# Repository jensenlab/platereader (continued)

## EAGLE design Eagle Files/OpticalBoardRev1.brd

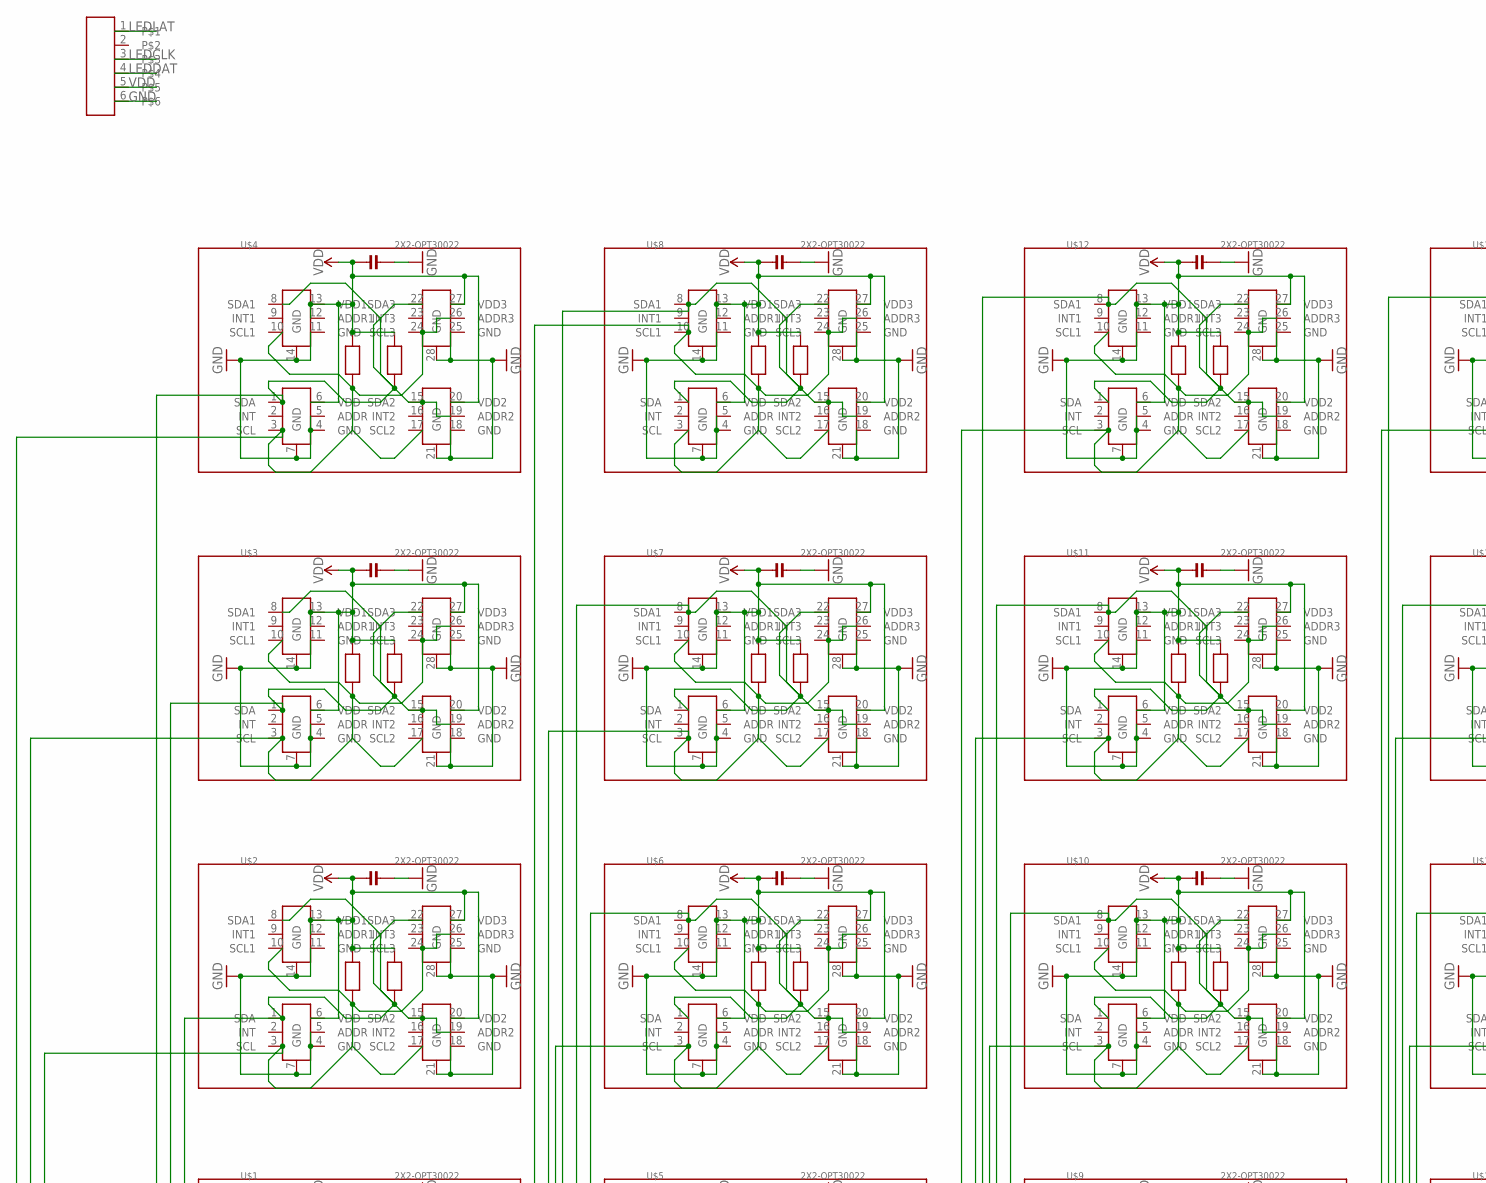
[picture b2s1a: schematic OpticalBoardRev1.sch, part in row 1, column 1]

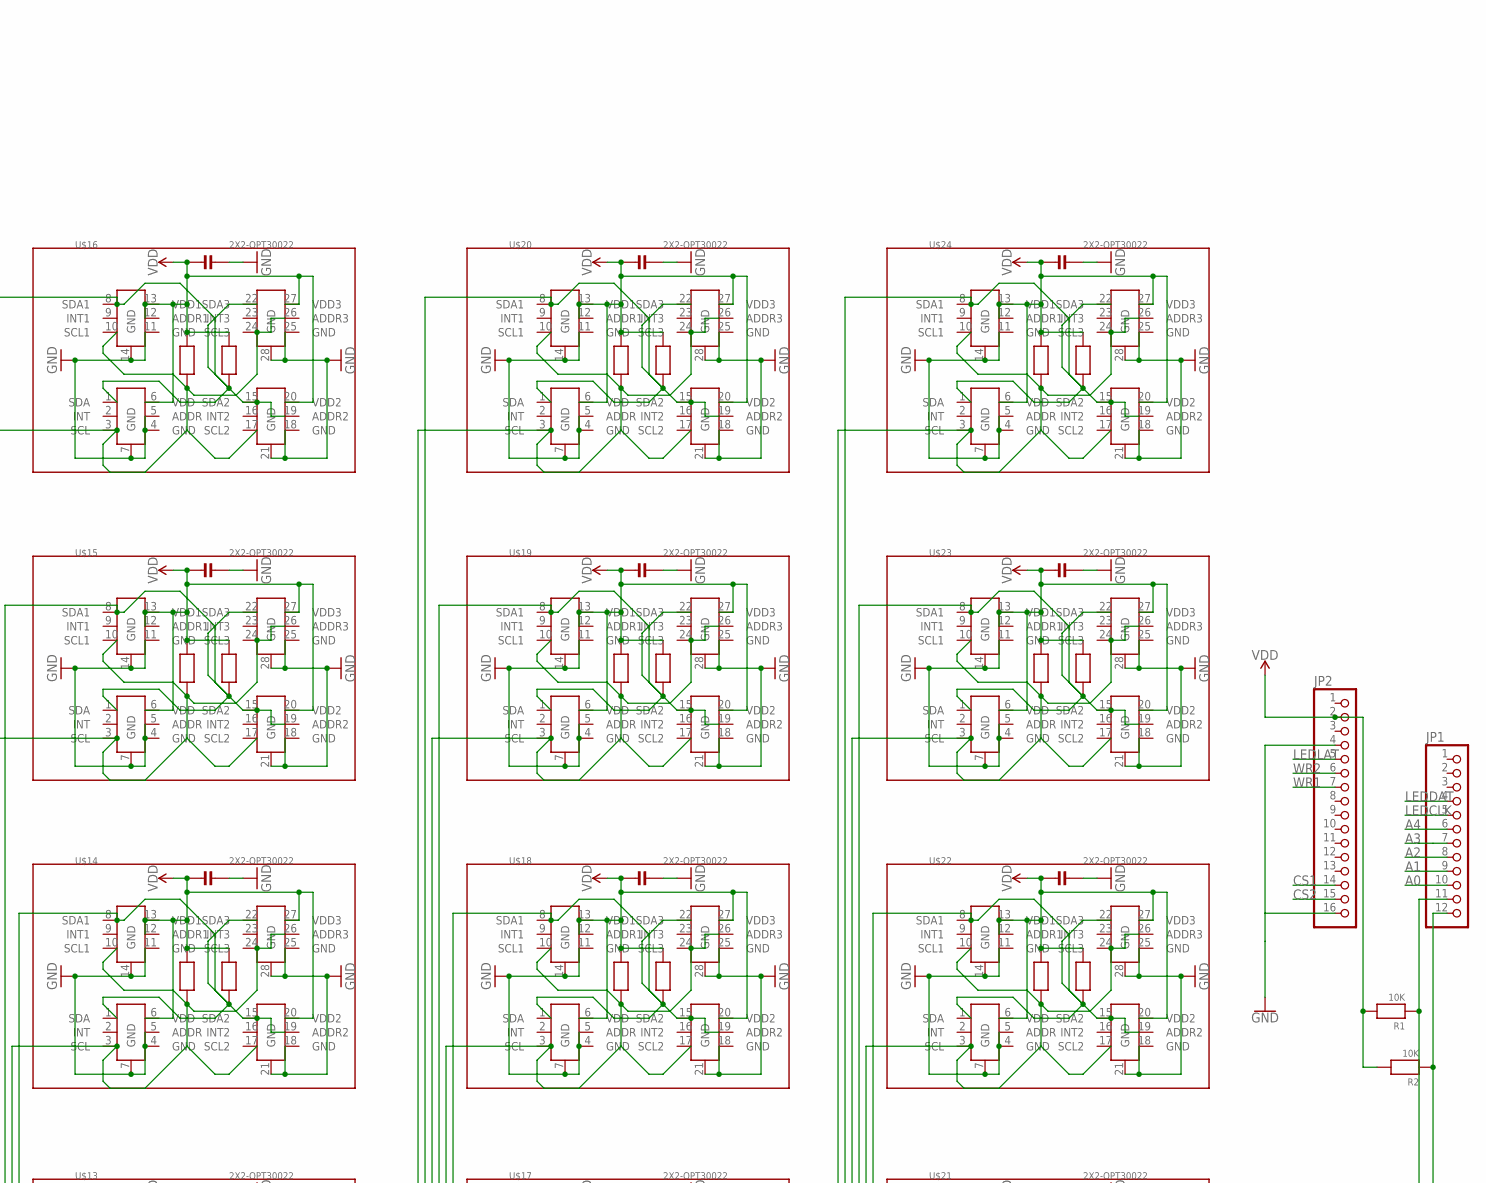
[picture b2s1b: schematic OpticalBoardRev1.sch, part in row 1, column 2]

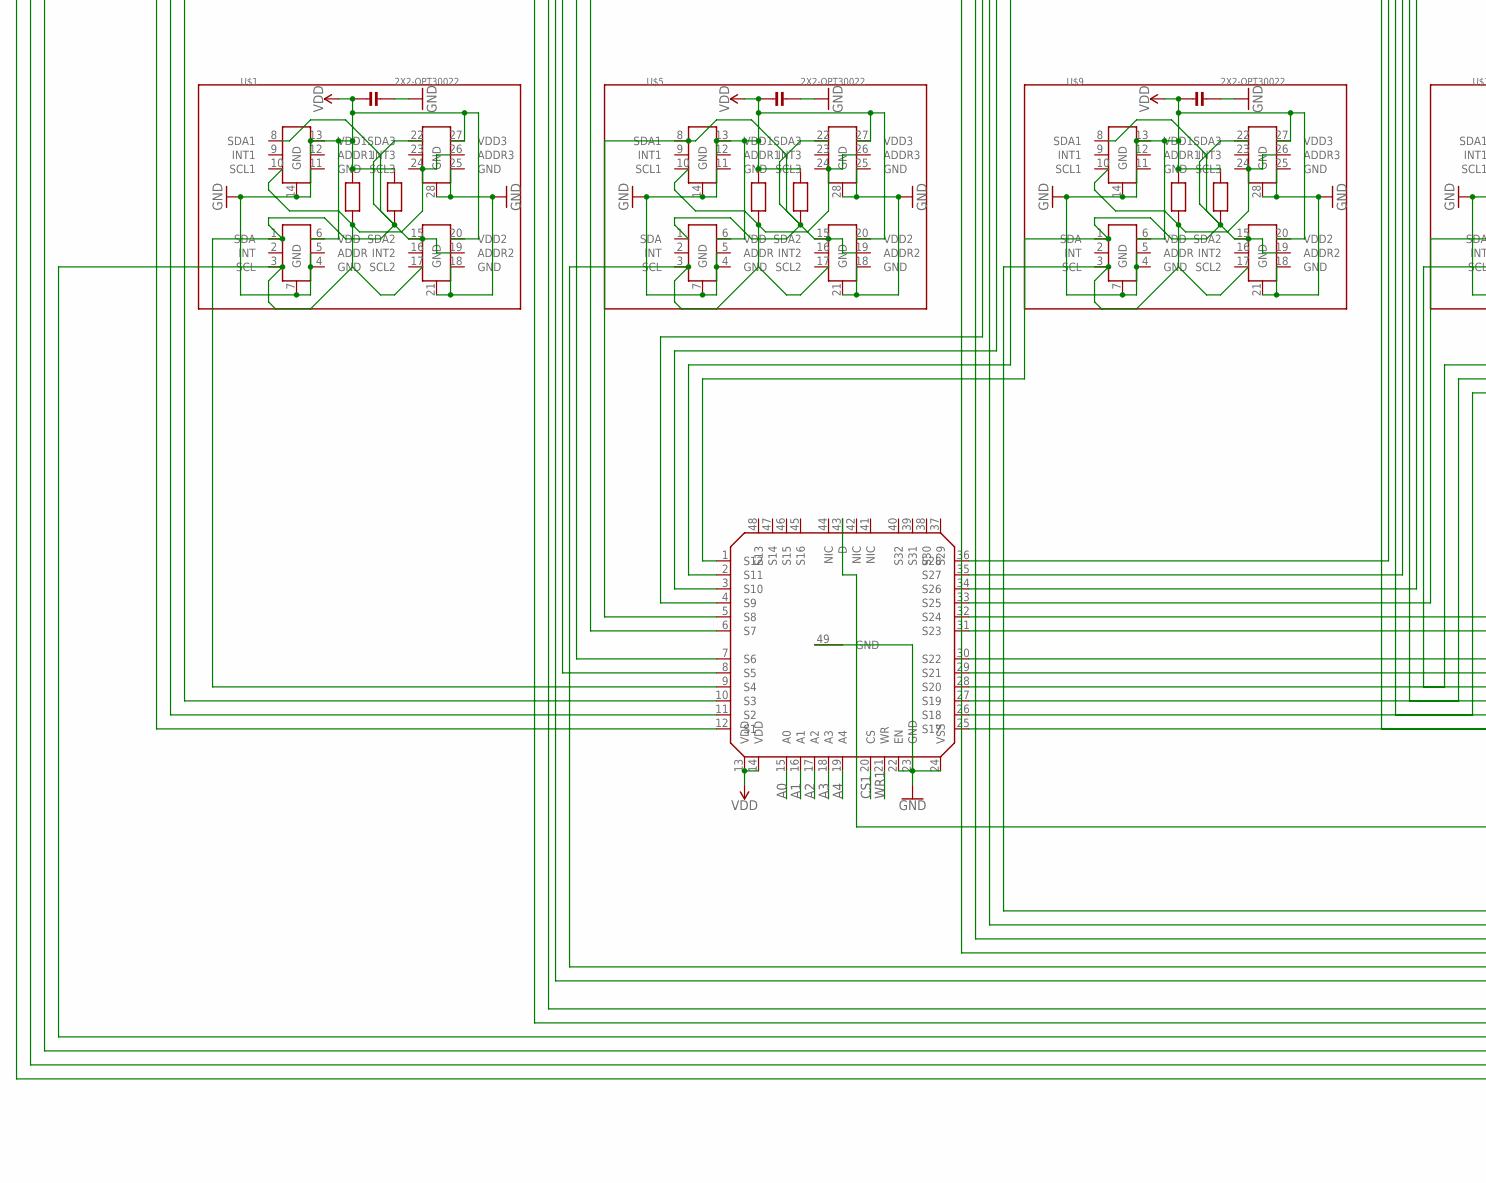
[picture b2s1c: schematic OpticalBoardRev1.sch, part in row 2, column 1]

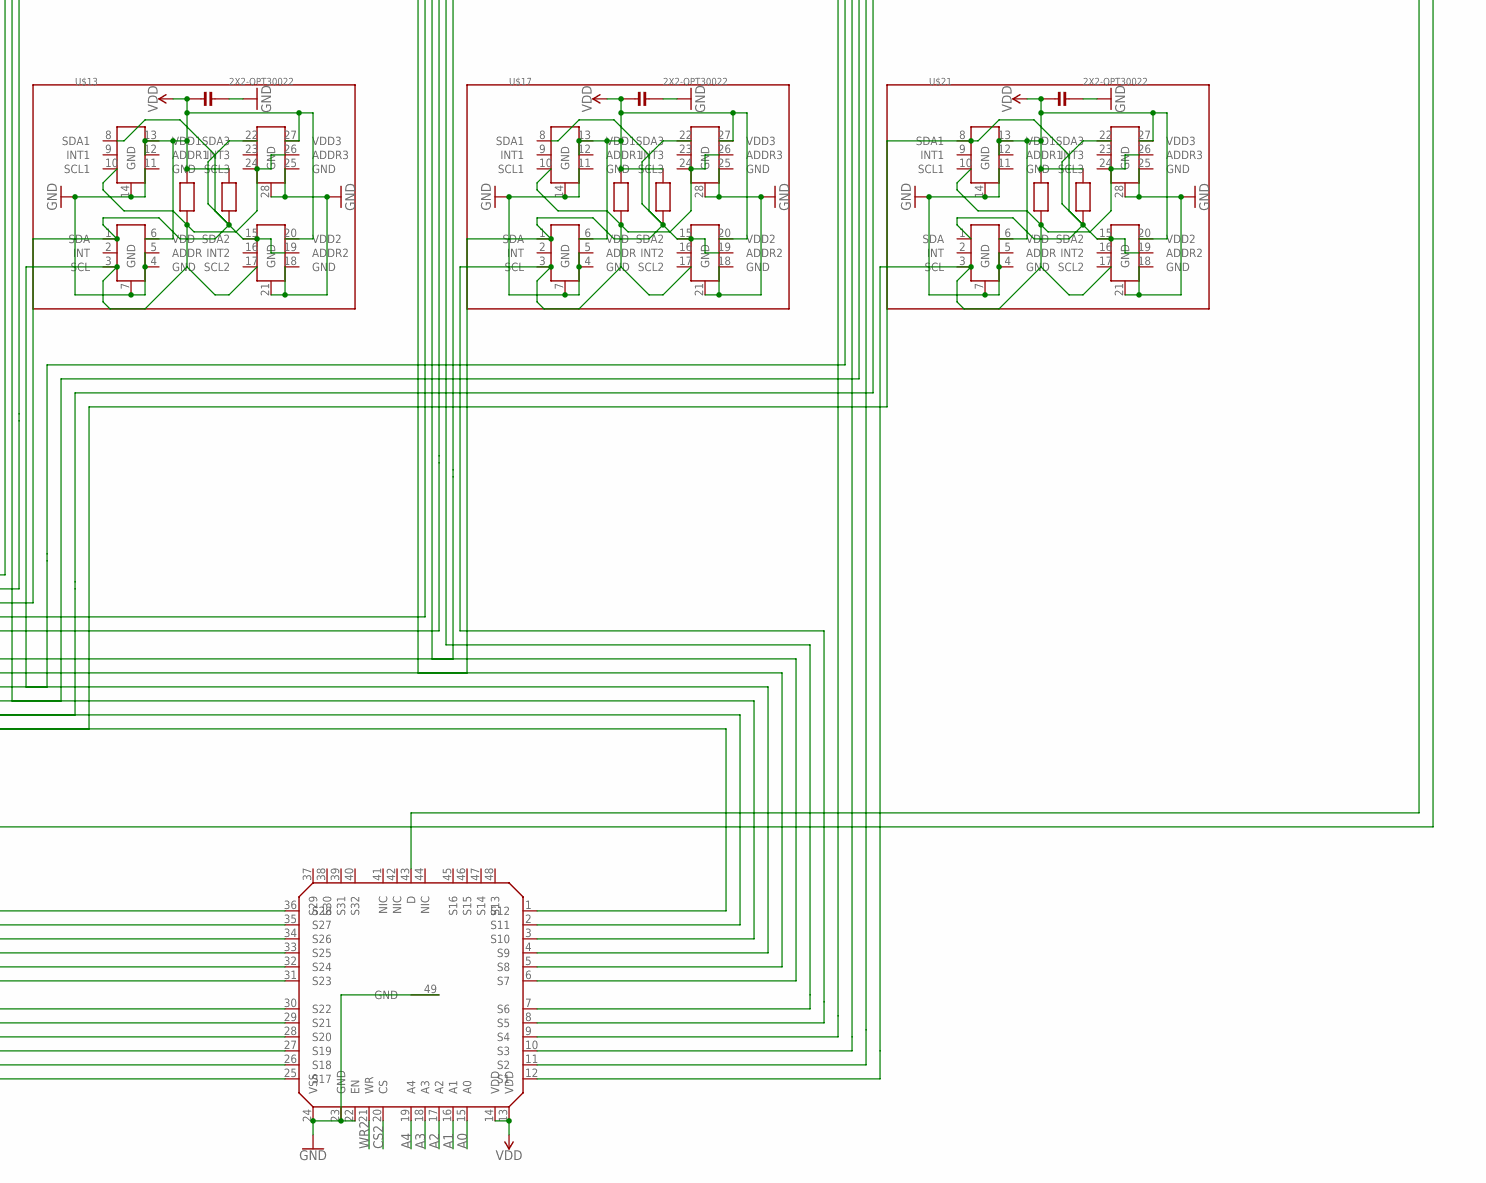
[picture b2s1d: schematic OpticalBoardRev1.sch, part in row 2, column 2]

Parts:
JP1: HEADER-1X12; 1X12_ROUND
JP2: HEADER-1X16ROUND; 1X16_ROUND
R1, R2: 10K; _0805
U$1, U$2, U$3, U$4, U$5, U$6, U$7, U$8, U$9, U$10, U$11, U$12, U$13, U$14, U$15, U$16, U$17, U$18, U$19, U$20, U$21, U$22, U$23, U$24: 2X2-OPT30022; 2X2-OPT3002-2
U$25: CONNECTOR_6PIN
U$26: 32MUXTOP; 32MUX
U$27: 32MUXBOT; 32MUX_BOT

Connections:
A0: JP1.10, U$26.15 (A0), U$27.15 (A0)
A1: JP1.9, U$26.16 (A1), U$27.16 (A1)
A2: JP1.8, U$26.17 (A2), U$27.17 (A2)
A3: JP1.7, U$26.18 (A3), U$27.18 (A3)
A4: JP1.6, U$26.19 (A4), U$27.19 (A4)
CS1: JP2.14, U$26.20 (CS)
CS2: JP2.15, U$27.20 (CS)
GND: JP2.4, JP2.16, U$1.4 (GND), U$1.5 (ADDR), U$1.7 (GND), U$1.11 (GND), U$1.14 (GND), U$1.18 (GND), U$1.21 (GND), U$1.25 (GND), U$1.28 (GND), U$1.30 (GND), U$2.4 (GND), U$2.5 (ADDR), U$2.7 (GND), U$2.11 (GND), U$2.14 (GND), U$2.18 (GND), U$2.21 (GND), U$2.25 (GND), U$2.28 (GND), U$2.30 (GND), U$3.4 (GND), U$3.5 (ADDR), U$3.7 (GND), U$3.11 (GND), U$3.14 (GND), U$3.18 (GND), U$3.21 (GND), U$3.25 (GND), U$3.28 (GND), U$3.30 (GND), U$4.4 (GND), U$4.5 (ADDR), U$4.7 (GND), U$4.11 (GND), U$4.14 (GND), U$4.18 (GND), U$4.21 (GND), U$4.25 (GND), U$4.28 (GND), U$4.30 (GND), U$5.4 (GND), U$5.5 (ADDR), U$5.7 (GND), U$5.11 (GND), U$5.14 (GND), U$5.18 (GND), U$5.21 (GND), U$5.25 (GND), U$5.28 (GND), U$5.30 (GND), U$6.4 (GND), U$6.5 (ADDR), U$6.7 (GND), U$6.11 (GND), U$6.14 (GND), U$6.18 (GND), U$6.21 (GND), U$6.25 (GND), U$6.28 (GND), U$6.30 (GND), U$7.4 (GND), U$7.5 (ADDR), U$7.7 (GND), U$7.11 (GND), U$7.14 (GND), U$7.18 (GND), U$7.21 (GND), U$7.25 (GND), U$7.28 (GND), U$7.30 (GND), U$8.4 (GND), U$8.5 (ADDR), U$8.7 (GND), U$8.11 (GND), U$8.14 (GND), U$8.18 (GND), U$8.21 (GND), U$8.25 (GND), U$8.28 (GND), U$8.30 (GND), U$9.4 (GND), U$9.5 (ADDR), U$9.7 (GND), U$9.11 (GND), U$9.14 (GND), U$9.18 (GND), U$9.21 (GND), U$9.25 (GND), U$9.28 (GND), U$9.30 (GND), U$10.4 (GND), U$10.5 (ADDR), U$10.7 (GND), U$10.11 (GND), U$10.14 (GND), U$10.18 (GND), U$10.21 (GND), U$10.25 (GND), U$10.28 (GND), U$10.30 (GND), U$11.4 (GND), U$11.5 (ADDR), U$11.7 (GND), U$11.11 (GND), U$11.14 (GND), U$11.18 (GND), U$11.21 (GND), U$11.25 (GND), U$11.28 (GND), U$11.30 (GND), U$12.4 (GND), U$12.5 (ADDR), U$12.7 (GND), U$12.11 (GND), U$12.14 (GND), U$12.18 (GND), U$12.21 (GND), U$12.25 (GND), U$12.28 (GND), U$12.30 (GND), U$13.4 (GND), U$13.5 (ADDR), U$13.7 (GND), U$13.11 (GND), U$13.14 (GND), U$13.18 (GND), U$13.21 (GND), U$13.25 (GND), U$13.28 (GND), U$13.30 (GND), U$14.4 (GND), U$14.5 (ADDR), U$14.7 (GND), U$14.11 (GND), U$14.14 (GND), U$14.18 (GND), U$14.21 (GND), U$14.25 (GND), U$14.28 (GND), U$14.30 (GND), U$15.4 (GND), U$15.5 (ADDR), U$15.7 (GND), U$15.11 (GND), U$15.14 (GND), U$15.18 (GND), U$15.21 (GND), U$15.25 (GND), U$15.28 (GND), U$15.30 (GND), U$16.4 (GND), U$16.5 (ADDR), U$16.7 (GND), U$16.11 (GND), U$16.14 (GND), U$16.18 (GND), U$16.21 (GND), U$16.25 (GND), U$16.28 (GND)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
LEDCLK: JP1.5, U$25.3
LEDDAT: JP1.4, U$25.4
LEDLAT: JP2.5, U$25.1
SCL1: U$1.3 (SCL), U$1.10 (SCL1), U$1.17 (SCL2), U$1.24 (SCL3), U$1.26 (ADDR3), U$1.31 (R1+), U$27.28 (S20)
SCL2: U$2.3 (SCL), U$2.10 (SCL1), U$2.17 (SCL2), U$2.24 (SCL3), U$2.26 (ADDR3), U$2.31 (R1+), U$27.27 (S19)
SCL3: U$3.3 (SCL), U$3.10 (SCL1), U$3.17 (SCL2), U$3.24 (SCL3), U$3.26 (ADDR3), U$3.31 (R1+), U$27.26 (S18)
SCL4: U$4.3 (SCL), U$4.10 (SCL1), U$4.17 (SCL2), U$4.24 (SCL3), U$4.26 (ADDR3), U$4.31 (R1+), U$27.25 (S17)
SCL5: U$5.3 (SCL), U$5.10 (SCL1), U$5.17 (SCL2), U$5.24 (SCL3), U$5.26 (ADDR3), U$5.31 (R1+), U$27.32 (S24)
SCL6: U$6.3 (SCL), U$6.10 (SCL1), U$6.17 (SCL2), U$6.24 (SCL3), U$6.26 (ADDR3), U$6.31 (R1+), U$27.31 (S23)
SCL7: U$7.3 (SCL), U$7.10 (SCL1), U$7.17 (SCL2), U$7.24 (SCL3), U$7.26 (ADDR3), U$7.31 (R1+), U$27.30 (S22)
SCL8: U$8.3 (SCL), U$8.10 (SCL1), U$8.17 (SCL2), U$8.24 (SCL3), U$8.26 (ADDR3), U$8.31 (R1+), U$27.29 (S21)
SCL9: U$9.3 (SCL), U$9.10 (SCL1), U$9.17 (SCL2), U$9.24 (SCL3), U$9.26 (ADDR3), U$9.31 (R1+), U$27.36 (S28)
SCL10: U$10.3 (SCL), U$10.10 (SCL1), U$10.17 (SCL2), U$10.24 (SCL3), U$10.26 (ADDR3), U$10.31 (R1+), U$27.35 (S27)
SCL11: U$11.3 (SCL), U$11.10 (SCL1), U$11.17 (SCL2), U$11.24 (SCL3), U$11.26 (ADDR3), U$11.31 (R1+), U$27.34 (S26)
SCL12: U$12.3 (SCL), U$12.10 (SCL1), U$12.17 (SCL2), U$12.24 (SCL3), U$12.26 (ADDR3), U$12.31 (R1+), U$27.33 (S25)
SCL13: U$13.3 (SCL), U$13.10 (SCL1), U$13.17 (SCL2), U$13.24 (SCL3), U$13.26 (ADDR3), U$13.31 (R1+), U$27.4 (S9)
SCL14: U$14.3 (SCL), U$14.10 (SCL1), U$14.17 (SCL2), U$14.24 (SCL3), U$14.26 (ADDR3), U$14.31 (R1+), U$27.3 (S10)
SCL15: U$15.3 (SCL), U$15.10 (SCL1), U$15.17 (SCL2), U$15.24 (SCL3), U$15.26 (ADDR3), U$15.31 (R1+), U$27.2 (S11)
SCL16: U$16.3 (SCL), U$16.10 (SCL1), U$16.17 (SCL2), U$16.24 (SCL3), U$16.26 (ADDR3), U$16.31 (R1+), U$27.1 (S12)
SCL17: U$17.3 (SCL), U$17.10 (SCL1), U$17.17 (SCL2), U$17.24 (SCL3), U$17.26 (ADDR3), U$17.31 (R1+), U$27.8 (S5)
SCL18: U$18.3 (SCL), U$18.10 (SCL1), U$18.17 (SCL2), U$18.24 (SCL3), U$18.26 (ADDR3), U$18.31 (R1+), U$27.7 (S6)
SCL19: U$19.3 (SCL), U$19.10 (SCL1), U$19.17 (SCL2), U$19.24 (SCL3), U$19.26 (ADDR3), U$19.31 (R1+), U$27.6 (S7)
SCL20: U$20.3 (SCL), U$20.10 (SCL1), U$20.17 (SCL2), U$20.24 (SCL3), U$20.26 (ADDR3), U$20.31 (R1+), U$27.5 (S8)
SCL21: U$21.3 (SCL), U$21.10 (SCL1), U$21.17 (SCL2), U$21.24 (SCL3), U$21.26 (ADDR3), U$21.31 (R1+), U$27.12 (S1)
SCL22: U$22.3 (SCL), U$22.10 (SCL1), U$22.17 (SCL2), U$22.24 (SCL3), U$22.26 (ADDR3), U$22.31 (R1+), U$27.11 (S2)
SCL23: U$23.3 (SCL), U$23.10 (SCL1), U$23.17 (SCL2), U$23.24 (SCL3), U$23.26 (ADDR3), U$23.31 (R1+), U$27.10 (S3)
SCL24: U$24.3 (SCL), U$24.10 (SCL1), U$24.17 (SCL2), U$24.24 (SCL3), U$24.26 (ADDR3), U$24.31 (R1+), U$27.9 (S4)
SCLK: JP1.11, R1.1, U$27.43 (D)
SDA1: U$1.1 (SDA), U$1.8 (SDA1), U$1.15 (SDA2), U$1.19 (ADDR2), U$1.22 (SDA3), U$1.33 (R2+), U$26.9 (S4)
SDA2: U$2.1 (SDA), U$2.8 (SDA1), U$2.15 (SDA2), U$2.19 (ADDR2), U$2.22 (SDA3), U$2.33 (R2+), U$26.10 (S3)
SDA3: U$3.1 (SDA), U$3.8 (SDA1), U$3.15 (SDA2), U$3.19 (ADDR2), U$3.22 (SDA3), U$3.33 (R2+), U$26.11 (S2)
SDA4: U$4.1 (SDA), U$4.8 (SDA1), U$4.15 (SDA2), U$4.19 (ADDR2), U$4.22 (SDA3), U$4.33 (R2+), U$26.12 (S1)
SDA5: U$5.1 (SDA), U$5.8 (SDA1), U$5.15 (SDA2), U$5.19 (ADDR2), U$5.22 (SDA3), U$5.33 (R2+), U$26.5 (S8)
SDA6: U$6.1 (SDA), U$6.8 (SDA1), U$6.15 (SDA2), U$6.19 (ADDR2), U$6.22 (SDA3), U$6.33 (R2+), U$26.6 (S7)
SDA7: U$7.1 (SDA), U$7.8 (SDA1), U$7.15 (SDA2), U$7.19 (ADDR2), U$7.22 (SDA3), U$7.33 (R2+), U$26.7 (S6)
SDA8: U$8.1 (SDA), U$8.8 (SDA1), U$8.15 (SDA2), U$8.19 (ADDR2), U$8.22 (SDA3), U$8.33 (R2+), U$26.8 (S5)
SDA9: U$9.1 (SDA), U$9.8 (SDA1), U$9.15 (SDA2), U$9.19 (ADDR2), U$9.22 (SDA3), U$9.33 (R2+), U$26.1 (S12)
SDA10: U$10.1 (SDA), U$10.8 (SDA1), U$10.15 (SDA2), U$10.19 (ADDR2), U$10.22 (SDA3), U$10.33 (R2+), U$26.2 (S11)
SDA11: U$11.1 (SDA), U$11.8 (SDA1), U$11.15 (SDA2), U$11.19 (ADDR2), U$11.22 (SDA3), U$11.33 (R2+), U$26.3 (S10)
SDA12: U$12.1 (SDA), U$12.8 (SDA1), U$12.15 (SDA2), U$12.19 (ADDR2), U$12.22 (SDA3), U$12.33 (R2+), U$26.4 (S9)
SDA13: U$13.1 (SDA), U$13.8 (SDA1), U$13.15 (SDA2), U$13.19 (ADDR2), U$13.22 (SDA3), U$13.33 (R2+), U$26.33 (S25)
SDA14: U$14.1 (SDA), U$14.8 (SDA1), U$14.15 (SDA2), U$14.19 (ADDR2), U$14.22 (SDA3), U$14.33 (R2+), U$26.34 (S26)
SDA15: U$15.1 (SDA), U$15.8 (SDA1), U$15.15 (SDA2), U$15.19 (ADDR2), U$15.22 (SDA3), U$15.33 (R2+), U$26.35 (S27)
SDA16: U$16.1 (SDA), U$16.8 (SDA1), U$16.15 (SDA2), U$16.19 (ADDR2), U$16.22 (SDA3), U$16.33 (R2+), U$26.36 (S28)
SDA17: U$17.1 (SDA), U$17.8 (SDA1), U$17.15 (SDA2), U$17.19 (ADDR2), U$17.22 (SDA3), U$17.33 (R2+), U$26.29 (S21)
SDA18: U$18.1 (SDA), U$18.8 (SDA1), U$18.15 (SDA2), U$18.19 (ADDR2), U$18.22 (SDA3), U$18.33 (R2+), U$26.30 (S22)
SDA19: U$19.1 (SDA), U$19.8 (SDA1), U$19.15 (SDA2), U$19.19 (ADDR2), U$19.22 (SDA3), U$19.33 (R2+), U$26.31 (S23)
SDA20: U$20.1 (SDA), U$20.8 (SDA1), U$20.15 (SDA2), U$20.19 (ADDR2), U$20.22 (SDA3), U$20.33 (R2+), U$26.32 (S24)
SDA21: U$21.1 (SDA), U$21.8 (SDA1), U$21.15 (SDA2), U$21.19 (ADDR2), U$21.22 (SDA3), U$21.33 (R2+), U$26.25 (S17)
SDA22: U$22.1 (SDA), U$22.8 (SDA1), U$22.15 (SDA2), U$22.19 (ADDR2), U$22.22 (SDA3), U$22.33 (R2+), U$26.26 (S18)
SDA23: U$23.1 (SDA), U$23.8 (SDA1), U$23.15 (SDA2), U$23.19 (ADDR2), U$23.22 (SDA3), U$23.33 (R2+), U$26.27 (S19)
SDA24: U$24.1 (SDA), U$24.8 (SDA1), U$24.15 (SDA2), U$24.19 (ADDR2), U$24.22 (SDA3), U$24.33 (R2+), U$26.28 (S20)
SDAT: JP1.12, R2.1, U$26.43 (D)
VDD: JP2.2, R1.2, R2.2, U$1.6 (VDD), U$1.12 (ADDR1), U$1.13 (VDD1), U$1.20 (VDD2), U$1.27 (VDD3), U$1.29 (C+), U$1.32 (GND), U$1.34 (GND), U$2.6 (VDD), U$2.12 (ADDR1), U$2.13 (VDD1), U$2.20 (VDD2), U$2.27 (VDD3), U$2.29 (C+), U$2.32 (GND), U$2.34 (GND), U$3.6 (VDD), U$3.12 (ADDR1), U$3.13 (VDD1), U$3.20 (VDD2), U$3.27 (VDD3), U$3.29 (C+), U$3.32 (GND), U$3.34 (GND), U$4.6 (VDD), U$4.12 (ADDR1), U$4.13 (VDD1), U$4.20 (VDD2), U$4.27 (VDD3), U$4.29 (C+), U$4.32 (GND), U$4.34 (GND), U$5.6 (VDD), U$5.12 (ADDR1), U$5.13 (VDD1), U$5.20 (VDD2), U$5.27 (VDD3), U$5.29 (C+), U$5.32 (GND), U$5.34 (GND), U$6.6 (VDD), U$6.12 (ADDR1), U$6.13 (VDD1), U$6.20 (VDD2), U$6.27 (VDD3), U$6.29 (C+), U$6.32 (GND), U$6.34 (GND), U$7.6 (VDD), U$7.12 (ADDR1), U$7.13 (VDD1), U$7.20 (VDD2), U$7.27 (VDD3), U$7.29 (C+), U$7.32 (GND), U$7.34 (GND), U$8.6 (VDD), U$8.12 (ADDR1), U$8.13 (VDD1), U$8.20 (VDD2), U$8.27 (VDD3), U$8.29 (C+), U$8.32 (GND), U$8.34 (GND), U$9.6 (VDD), U$9.12 (ADDR1), U$9.13 (VDD1), U$9.20 (VDD2), U$9.27 (VDD3), U$9.29 (C+), U$9.32 (GND), U$9.34 (GND), U$10.6 (VDD), U$10.12 (ADDR1), U$10.13 (VDD1), U$10.20 (VDD2), U$10.27 (VDD3), U$10.29 (C+), U$10.32 (GND), U$10.34 (GND), U$11.6 (VDD), U$11.12 (ADDR1), U$11.13 (VDD1), U$11.20 (VDD2), U$11.27 (VDD3), U$11.29 (C+), U$11.32 (GND), U$11.34 (GND), U$12.6 (VDD), U$12.12 (ADDR1), U$12.13 (VDD1), U$12.20 (VDD2), U$12.27 (VDD3), U$12.29 (C+), U$12.32 (GND), U$12.34 (GND), U$13.6 (VDD), U$13.12 (ADDR1), U$13.13 (VDD1), U$13.20 (VDD2), U$13.27 (VDD3), U$13.29 (C+), U$13.32 (GND), U$13.34 (GND), U$14.6 (VDD), U$14.12 (ADDR1), U$14.13 (VDD1), U$14.20 (VDD2), U$14.27 (VDD3), U$14.29 (C+), U$14.32 (GND), U$14.34 (GND), U$15.6 (VDD), U$15.12 (ADDR1), U$15.13 (VDD1), U$15.20 (VDD2), U$15.27 (VDD3), U$15.29 (C+), U$15.32 (GND), U$15.34 (GND), U$16.6 (VDD), U$16.12 (ADDR1), U$16.13 (VDD1), U$16.20 (VDD2), U$16.27 (VDD3), U$16.29 (C+), U$16.32 (GND), U$16.34 (GND), U$17.6 (VDD), U$17.12 (ADDR1), U$17.13 (VDD1), U$17.20 (VDD2), U$17.27 (VDD3), U$17.29 (C+), U$17.32 (GND), U$17.34 (GND), U$18.6 (VDD), U$18.12 (ADDR1), U$18.13 (VDD1), U$18.20 (VDD2), U$18.27 (VDD3), U$18.29 (C+), U$18.32 (GND), U$18.34 (GND), U$19.6 (VDD), U$19.12 (ADDR1), U$19.13 (VDD1), U$19.20 (VDD2), U$19.27 (VDD3), U$19.29 (C+), U$19.32 (GND), U$19.34 (GND), U$20.6 (VDD), U$20.12 (ADDR1), U$20.13 (VDD1), U$20.20 (VDD2), U$20.27 (VDD3), U$20.29 (C+)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
WR1: JP2.7, U$26.21 (WR)
WR2: JP2.6, U$27.21 (WR)

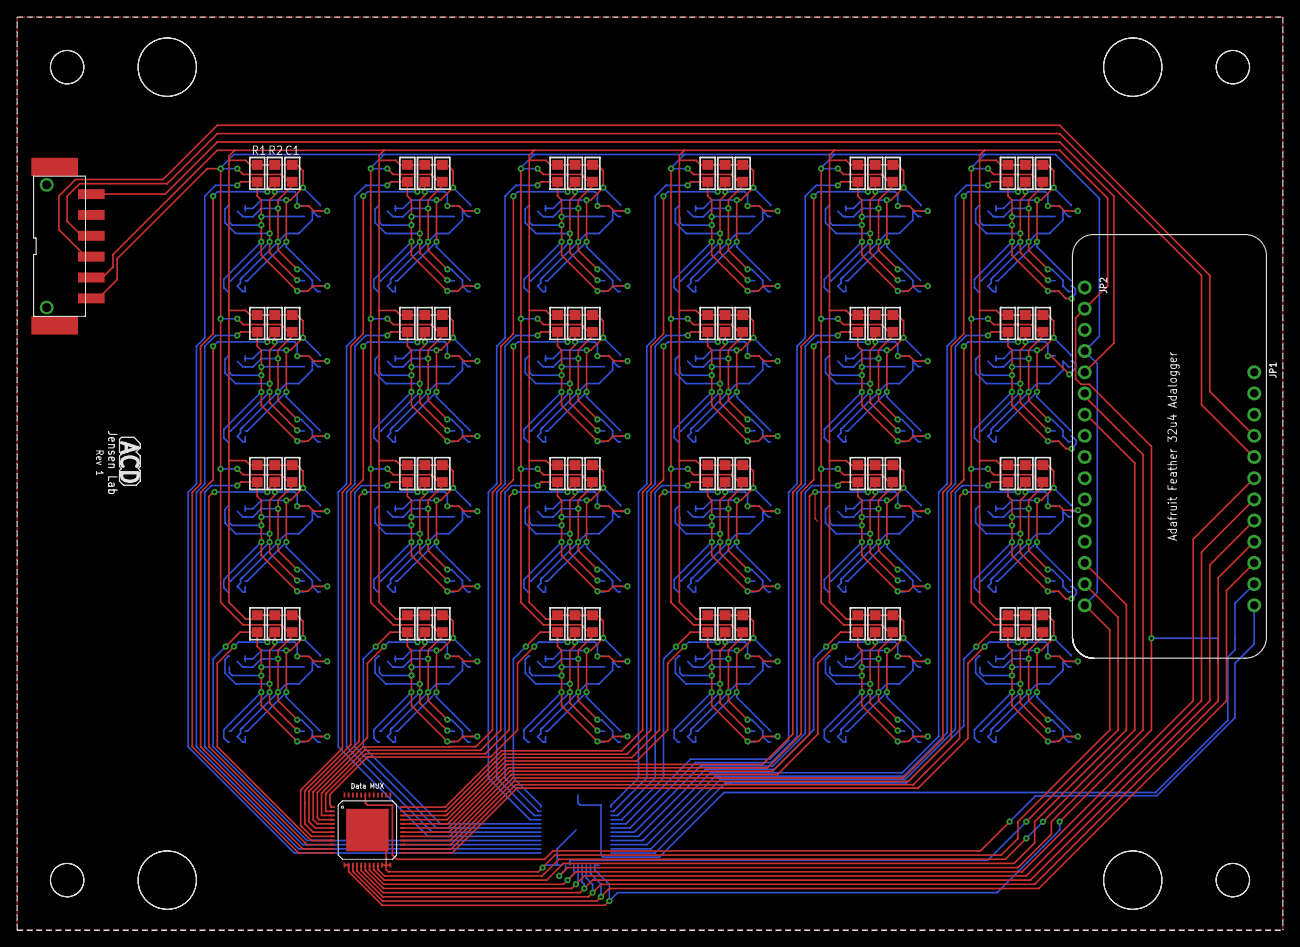
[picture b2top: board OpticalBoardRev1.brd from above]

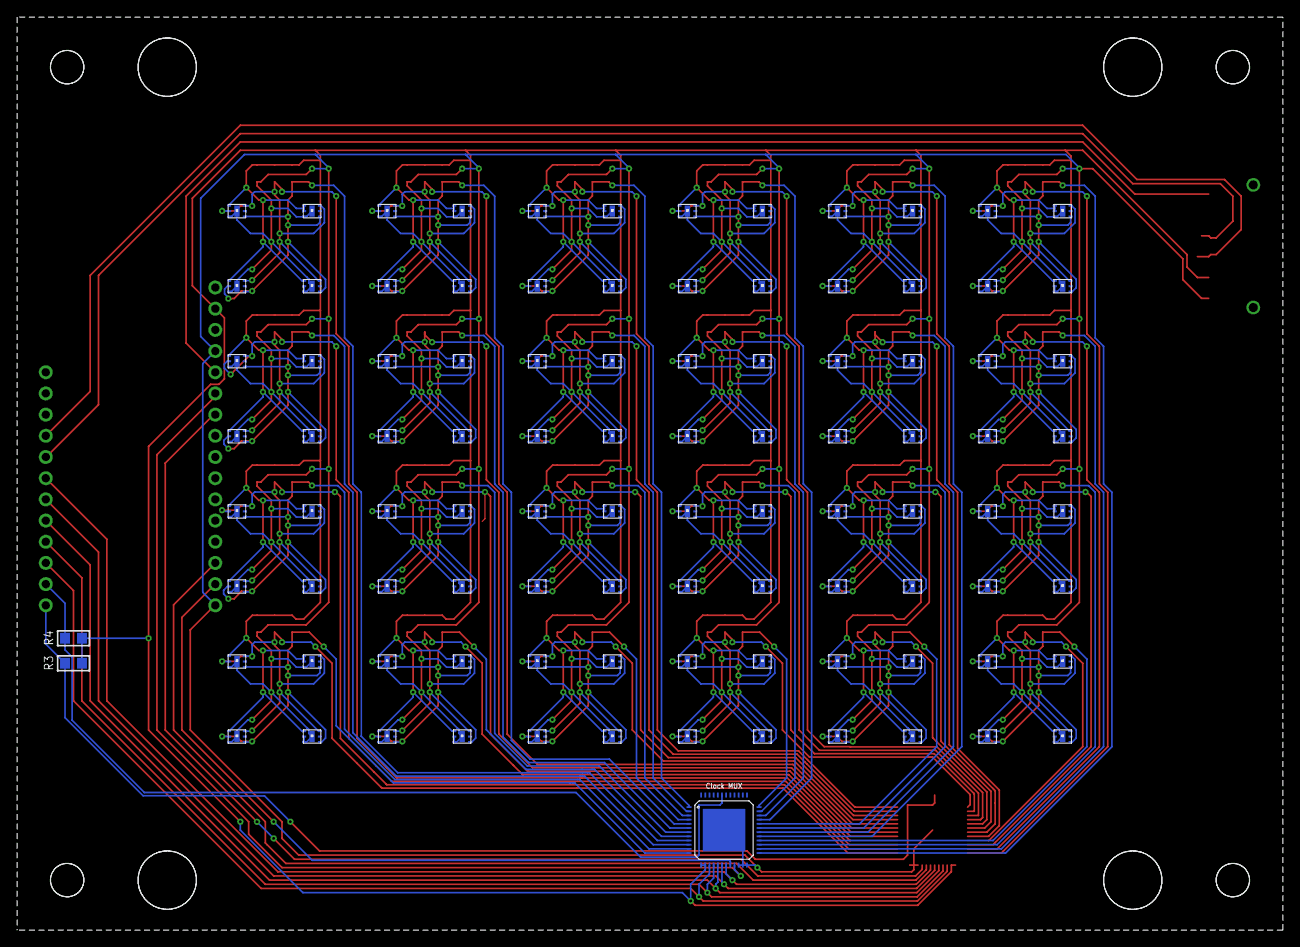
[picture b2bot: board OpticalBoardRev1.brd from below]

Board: 2 copper layers, 151.8 x 109.5 mm, 31 parts (2 on the bottom side), 64 nets.

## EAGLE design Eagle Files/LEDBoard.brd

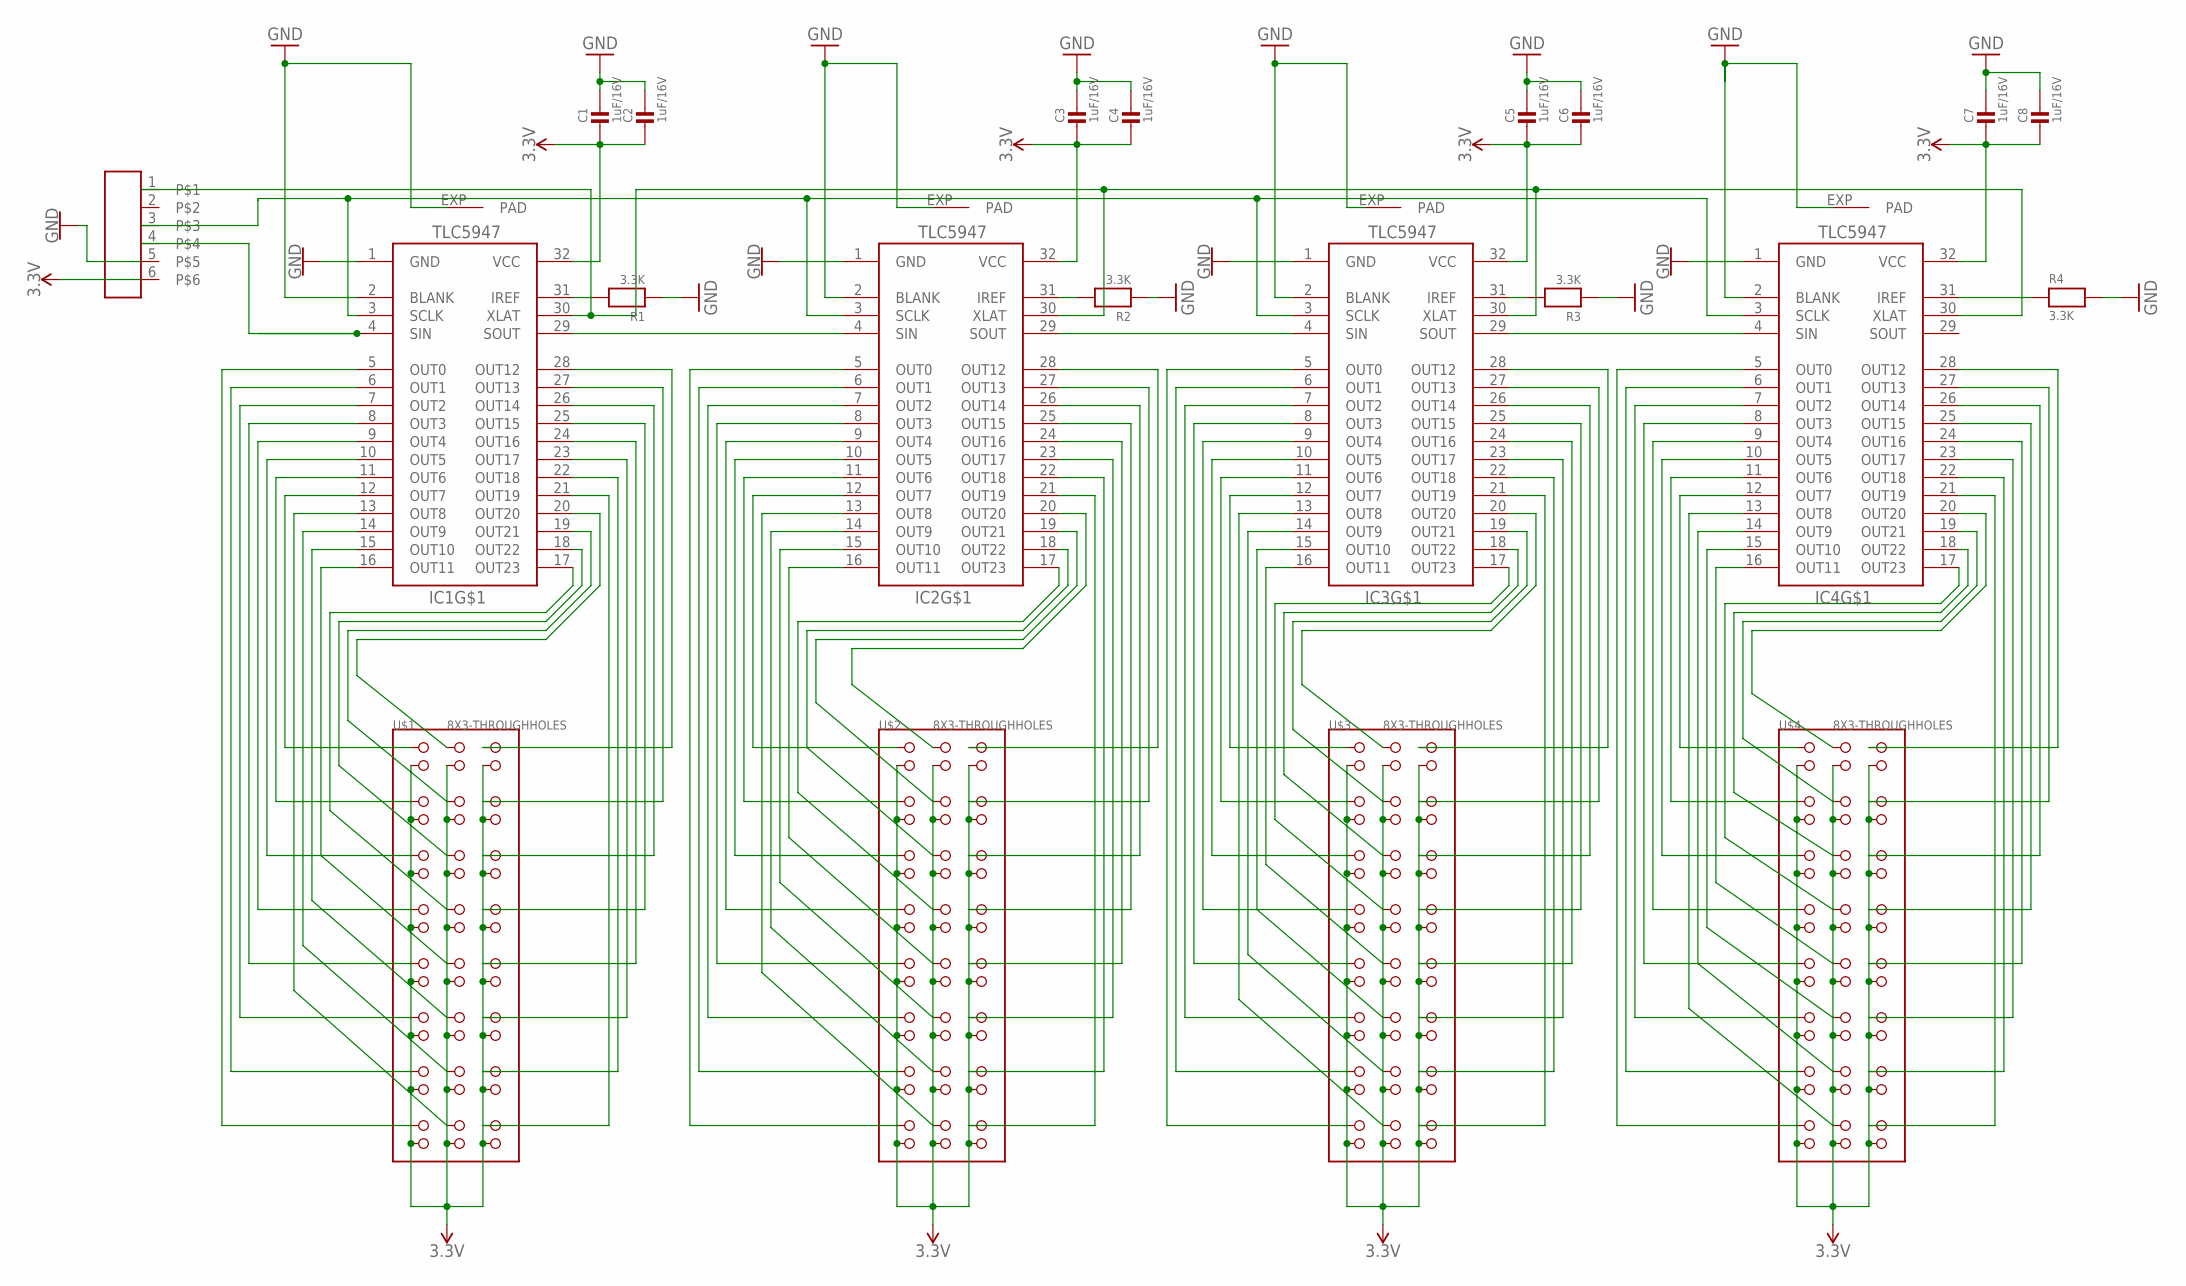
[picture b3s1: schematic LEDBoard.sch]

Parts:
C1, C2, C3, C4, C5, C6, C7, C8: 1uF/16V; _0805
IC1, IC2, IC3, IC4: TLC5947-DAP; HTSSOP32DAP
R1, R2, R3, R4: 3.3K; _0805
U$1, U$2, U$3, U$4: 8X3-THROUGHHOLES; COLUMNOFTHROUGHHOLES
U$5: CONNECTOR_6PIN

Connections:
0: IC1.5 (OUT0), U$1.0
1: IC1.6 (OUT1), U$1.1
2: IC1.7 (OUT2), U$1.2
3: IC1.8 (OUT3), U$1.3
3.3V: C1.2, C2.2, C3.2, C4.2, C5.2, C6.2, C7.2, C8.2, IC1.32 (VCC), IC2.32 (VCC), IC3.32 (VCC), IC4.32 (VCC), U$1.V0 (V), U$1.V1 (V), U$1.V2 (V), U$1.V3 (V), U$1.V4 (V), U$1.V5 (V), U$1.V6 (V), U$1.V7 (V), U$1.V8 (V), U$1.V9 (V), U$1.V10 (V), U$1.V11 (V), U$1.V12 (V), U$1.V13 (V), U$1.V14 (V), U$1.V15 (V), U$1.V16 (V), U$1.V17 (V), U$1.V18 (V), U$1.V19 (V), U$1.V20 (V), U$1.V21 (V), U$1.V22 (V), U$1.V23 (V), U$2.V0 (V), U$2.V1 (V), U$2.V2 (V), U$2.V3 (V), U$2.V4 (V), U$2.V5 (V), U$2.V6 (V), U$2.V7 (V), U$2.V8 (V), U$2.V9 (V), U$2.V10 (V), U$2.V11 (V), U$2.V12 (V), U$2.V13 (V), U$2.V14 (V), U$2.V15 (V), U$2.V16 (V), U$2.V17 (V), U$2.V18 (V), U$2.V19 (V), U$2.V20 (V), U$2.V21 (V), U$2.V22 (V), U$2.V23 (V), U$3.V0 (V), U$3.V1 (V), U$3.V2 (V), U$3.V3 (V), U$3.V4 (V), U$3.V5 (V), U$3.V6 (V), U$3.V7 (V), U$3.V8 (V), U$3.V9 (V), U$3.V10 (V), U$3.V11 (V), U$3.V12 (V), U$3.V13 (V), U$3.V14 (V), U$3.V15 (V), U$3.V16 (V), U$3.V17 (V), U$3.V18 (V), U$3.V19 (V), U$3.V20 (V), U$3.V21 (V), U$3.V22 (V), U$3.V23 (V), U$4.V0 (V), U$4.V1 (V), U$4.V2 (V), U$4.V3 (V), U$4.V4 (V), U$4.V5 (V), U$4.V6 (V), U$4.V7 (V), U$4.V8 (V), U$4.V9 (V), U$4.V10 (V), U$4.V11 (V), U$4.V12 (V), U$4.V13 (V), U$4.V14 (V), U$4.V15 (V), U$4.V16 (V), U$4.V17 (V), U$4.V18 (V), U$4.V19 (V), U$4.V20 (V), U$4.V21 (V), U$4.V22 (V), U$4.V23 (V), U$5.6
4: IC1.9 (OUT4), U$1.4
5: IC1.10 (OUT5), U$1.5
6: IC1.11 (OUT6), U$1.6
7: IC1.12 (OUT7), U$1.7
8: IC1.13 (OUT8), U$1.8
9: IC1.14 (OUT9), U$1.9
10: IC1.15 (OUT10), U$1.10
11: IC1.16 (OUT11), U$1.11
12: IC1.17 (OUT23), U$1.12
13: IC1.18 (OUT22), U$1.13
14: IC1.19 (OUT21), U$1.14
15: IC1.20 (OUT20), U$1.15
16: IC1.21 (OUT19), U$1.16
17: IC1.22 (OUT18), U$1.17
18: IC1.23 (OUT17), U$1.18
19: IC1.24 (OUT16), U$1.19
20: IC1.25 (OUT15), U$1.20
21: IC1.26 (OUT14), U$1.21
22: IC1.27 (OUT13), U$1.22
23: IC1.28 (OUT12), U$1.23
24: IC2.5 (OUT0), U$2.0
25: IC2.6 (OUT1), U$2.1
26: IC2.7 (OUT2), U$2.2
27: IC2.8 (OUT3), U$2.3
28: IC2.9 (OUT4), U$2.4
29: IC2.10 (OUT5), U$2.5
30: IC2.11 (OUT6), U$2.6
31: IC2.12 (OUT7), U$2.7
32: IC2.13 (OUT8), U$2.8
33: IC2.14 (OUT9), U$2.9
34: IC2.15 (OUT10), U$2.10
35: IC2.16 (OUT11), U$2.11
36: IC2.17 (OUT23), U$2.12
37: IC2.18 (OUT22), U$2.13
38: IC2.19 (OUT21), U$2.14
39: IC2.20 (OUT20), U$2.15
40: IC2.21 (OUT19), U$2.16
41: IC2.22 (OUT18), U$2.17
42: IC2.23 (OUT17), U$2.18
43: IC2.24 (OUT16), U$2.19
44: IC2.25 (OUT15), U$2.20
45: IC2.26 (OUT14), U$2.21
46: IC2.27 (OUT13), U$2.22
47: IC2.28 (OUT12), U$2.23
48: IC3.5 (OUT0), U$3.0
49: IC3.6 (OUT1), U$3.1
50: IC3.7 (OUT2), U$3.2
51: IC3.8 (OUT3), U$3.3
52: IC3.9 (OUT4), U$3.4
53: IC3.10 (OUT5), U$3.5
54: IC3.11 (OUT6), U$3.6
55: IC3.12 (OUT7), U$3.7
56: IC3.13 (OUT8), U$3.8
57: IC3.14 (OUT9), U$3.9
58: IC3.15 (OUT10), U$3.10
59: IC3.16 (OUT11), U$3.11
60: IC3.17 (OUT23), U$3.12
61: IC3.18 (OUT22), U$3.13
62: IC3.19 (OUT21), U$3.14
63: IC3.20 (OUT20), U$3.15
64: IC3.21 (OUT19), U$3.16
65: IC3.22 (OUT18), U$3.17
66: IC3.23 (OUT17), U$3.18
67: IC3.24 (OUT16), U$3.19
68: IC3.25 (OUT15), U$3.20
69: IC3.26 (OUT14), U$3.21
70: IC3.27 (OUT13), U$3.22
71: IC3.28 (OUT12), U$3.23
72: IC4.5 (OUT0), U$4.0
73: IC4.6 (OUT1), U$4.1
74: IC4.7 (OUT2), U$4.2
75: IC4.8 (OUT3), U$4.3
76: IC4.9 (OUT4), U$4.4
77: IC4.10 (OUT5), U$4.5
78: IC4.11 (OUT6), U$4.6
79: IC4.12 (OUT7), U$4.7
80: IC4.13 (OUT8), U$4.8
81: IC4.14 (OUT9), U$4.9
82: IC4.15 (OUT10), U$4.10
83: IC4.16 (OUT11), U$4.11
84: IC4.17 (OUT23), U$4.12
85: IC4.18 (OUT22), U$4.13
86: IC4.19 (OUT21), U$4.14
87: IC4.20 (OUT20), U$4.15
88: IC4.21 (OUT19), U$4.16
89: IC4.22 (OUT18), U$4.17
90: IC4.23 (OUT17), U$4.18
91: IC4.24 (OUT16), U$4.19
92: IC4.25 (OUT15), U$4.20
93: IC4.26 (OUT14), U$4.21
94: IC4.27 (OUT13), U$4.22
95: IC4.28 (OUT12), U$4.23
CLK: IC1.3 (SCLK), IC2.3 (SCLK), IC3.3 (SCLK), IC4.3 (SCLK), U$5.3
DATA12: IC1.29 (SOUT), IC2.4 (SIN)
DATA23: IC2.29 (SOUT), IC3.4 (SIN)
DATA34: IC3.29 (SOUT), IC4.4 (SIN)
DATAIN: IC1.4 (SIN), U$5.4
GND: C1.1, C2.1, C3.1, C4.1, C5.1, C6.1, C7.1, C8.1, IC1.1 (GND), IC1.2 (BLANK), IC1.EXP (PAD), IC2.1 (GND), IC2.2 (BLANK), IC2.EXP (PAD), IC3.1 (GND), IC3.2 (BLANK), IC3.EXP (PAD), IC4.1 (GND), IC4.2 (BLANK), IC4.EXP (PAD), R1.1, R2.1, R3.1, R4.2, U$5.5
IREF1: IC1.31 (IREF), R1.2
IREF2: IC2.31 (IREF), R2.2
IREF3: IC3.31 (IREF), R3.2
IREF4: IC4.31 (IREF), R4.1
XLAT: IC1.30 (XLAT), IC2.30 (XLAT), IC3.30 (XLAT), IC4.30 (XLAT), U$5.1

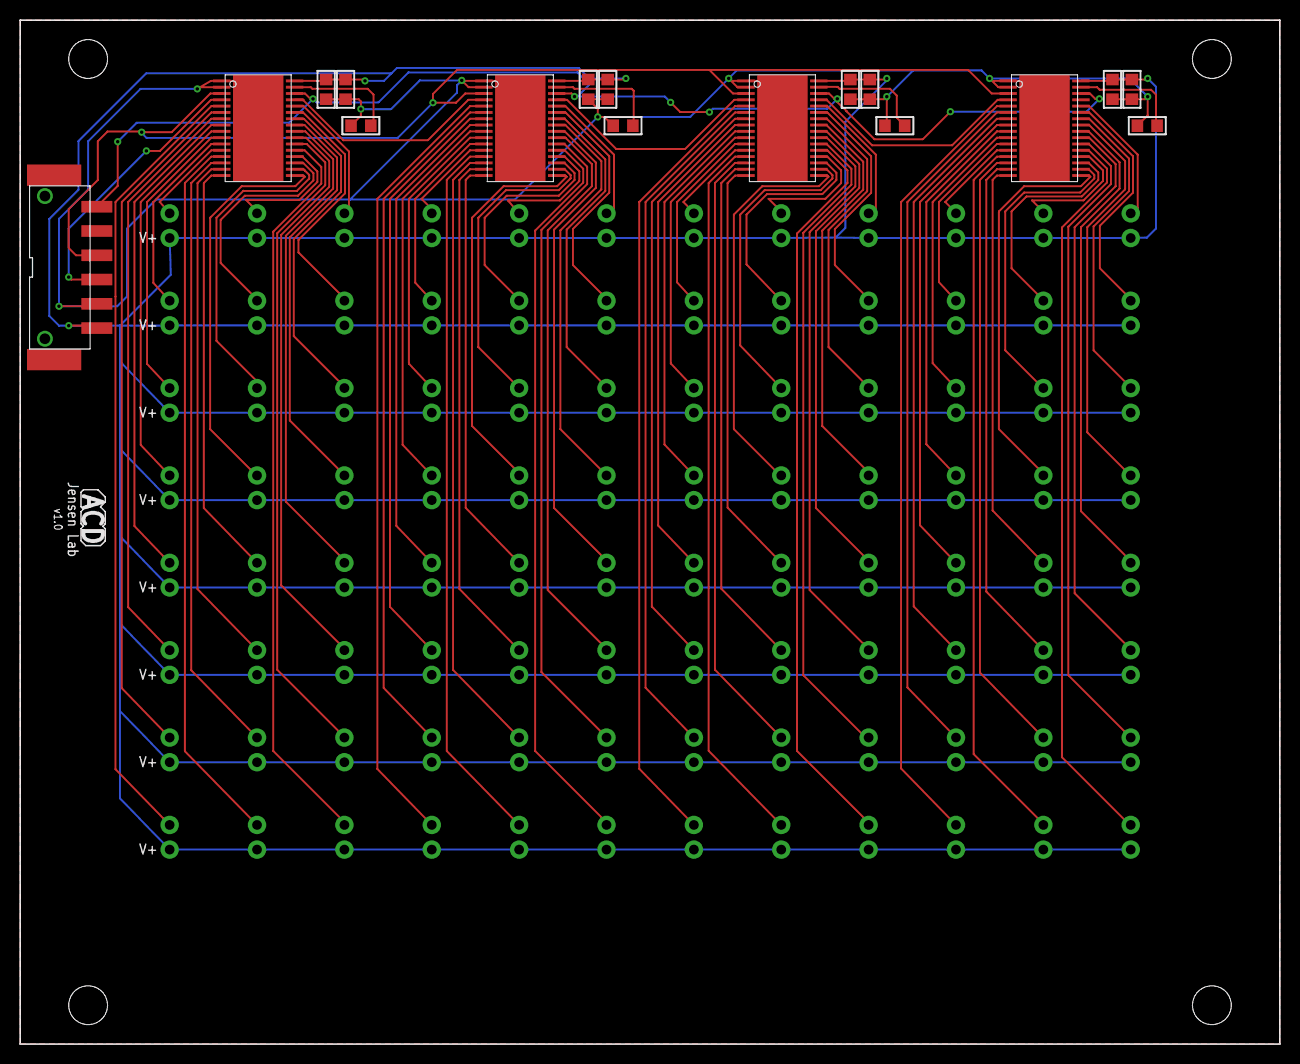
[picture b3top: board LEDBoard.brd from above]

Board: 2 copper layers, 129.8 x 105.5 mm, 21 parts (0 on the bottom side), 108 nets.

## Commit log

2017-10-24 Create temp
2017-10-24 Rename LEDBoard.brd to Eagle Files/LEDBoard.brd
2017-10-24 Rename LEDBoard.sch to Eagle Files/LEDBoard.sch
2017-10-24 Rename OpticalBoardRev1.brd to Eagle Files/OpticalBoardRev1.brd
2017-10-24 Rename OpticalBoardRev1.sch to Eagle Files/OpticalBoardRev1.sch
2017-10-24 Rename OpticalBoardRev2.brd to Eagle Files/OpticalBoardRev2.brd
2017-10-24 Rename OpticalBoardRev2.sch to Eagle Files/OpticalBoardRev2.sch
2017-10-24 Rename TIcustom.lbr to Eagle Files/TIcustom.lbr
